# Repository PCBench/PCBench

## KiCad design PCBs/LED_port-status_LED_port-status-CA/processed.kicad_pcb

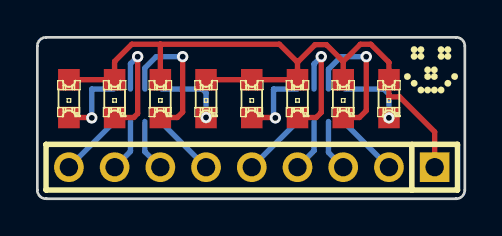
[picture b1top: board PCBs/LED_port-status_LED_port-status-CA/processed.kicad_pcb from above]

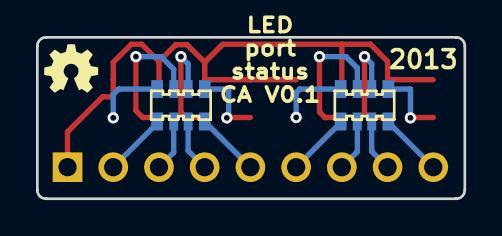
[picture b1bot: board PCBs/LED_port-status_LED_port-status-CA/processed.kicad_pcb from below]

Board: 2 copper layers, 23.7 x 9.0 mm, 13 parts (3 on the bottom side), 17 nets.

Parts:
D1, D2, D3, D4, D5, D6, D7, D8: LED; LED-0805
G1: LED_smile_silkscreen_3mm
G2: OSHW-logo_silkscreen_3mm
P1: CONN_9; SIL-9
RP1, RP2: 1k; MADW__1206*4_resistor_array

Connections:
unnamed: P1.9, RP1.4
unnamed: P1.8, RP1.3
unnamed: P1.7, RP1.2
unnamed: P1.6, RP1.1
unnamed: P1.5, RP2.4
unnamed: P1.4, RP2.3
unnamed: P1.3, RP2.2
unnamed: P1.2, RP2.1
unnamed: D1.2, RP1.5
unnamed: D6.2, RP2.6
unnamed: D8.2, RP2.8
unnamed: D5.2, RP2.5
unnamed: D4.2, RP1.8
unnamed: D2.2, RP1.6
unnamed: D7.2, RP2.7
unnamed: D3.2, RP1.7
unnamed: D1.1, D2.1, D3.1, D4.1, D5.1, D6.1, D7.1, D8.1, P1.1

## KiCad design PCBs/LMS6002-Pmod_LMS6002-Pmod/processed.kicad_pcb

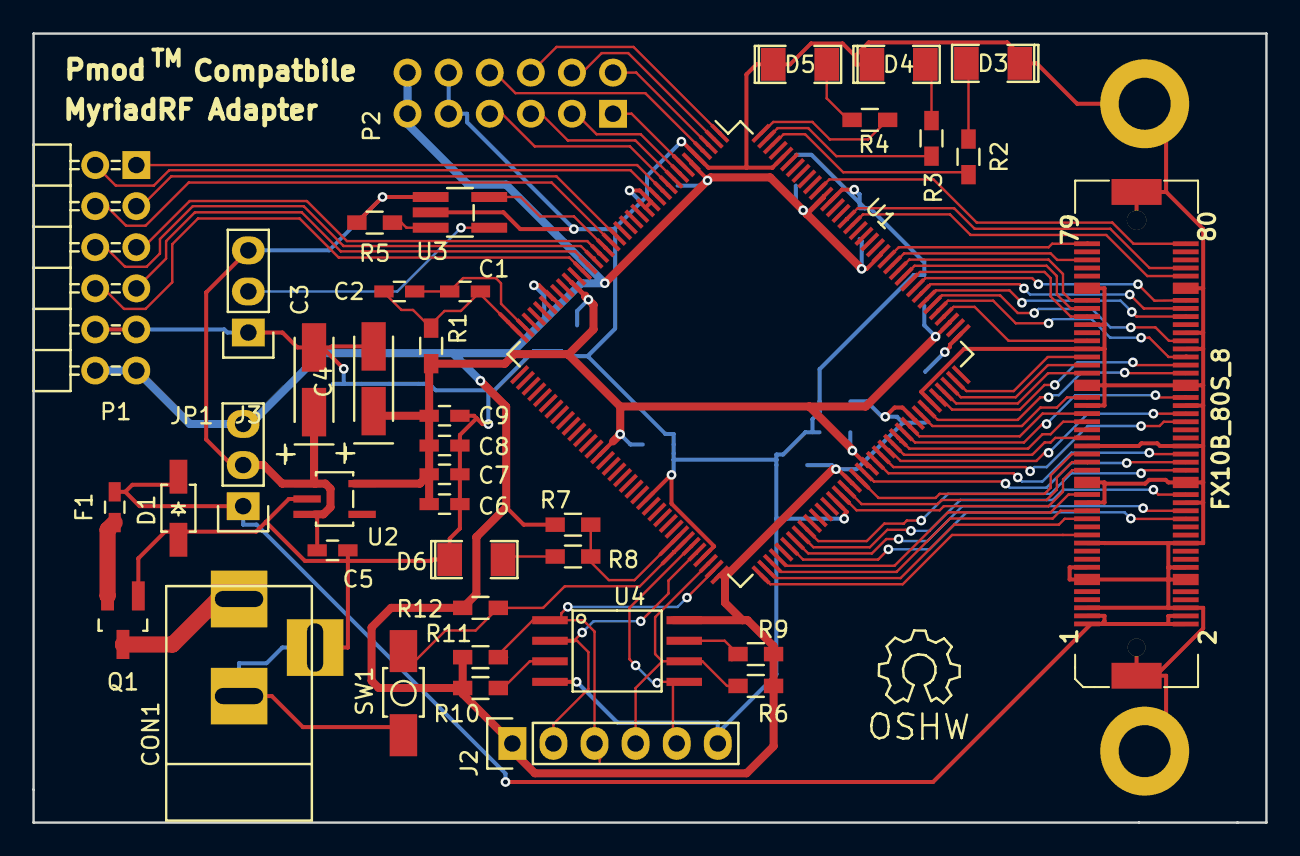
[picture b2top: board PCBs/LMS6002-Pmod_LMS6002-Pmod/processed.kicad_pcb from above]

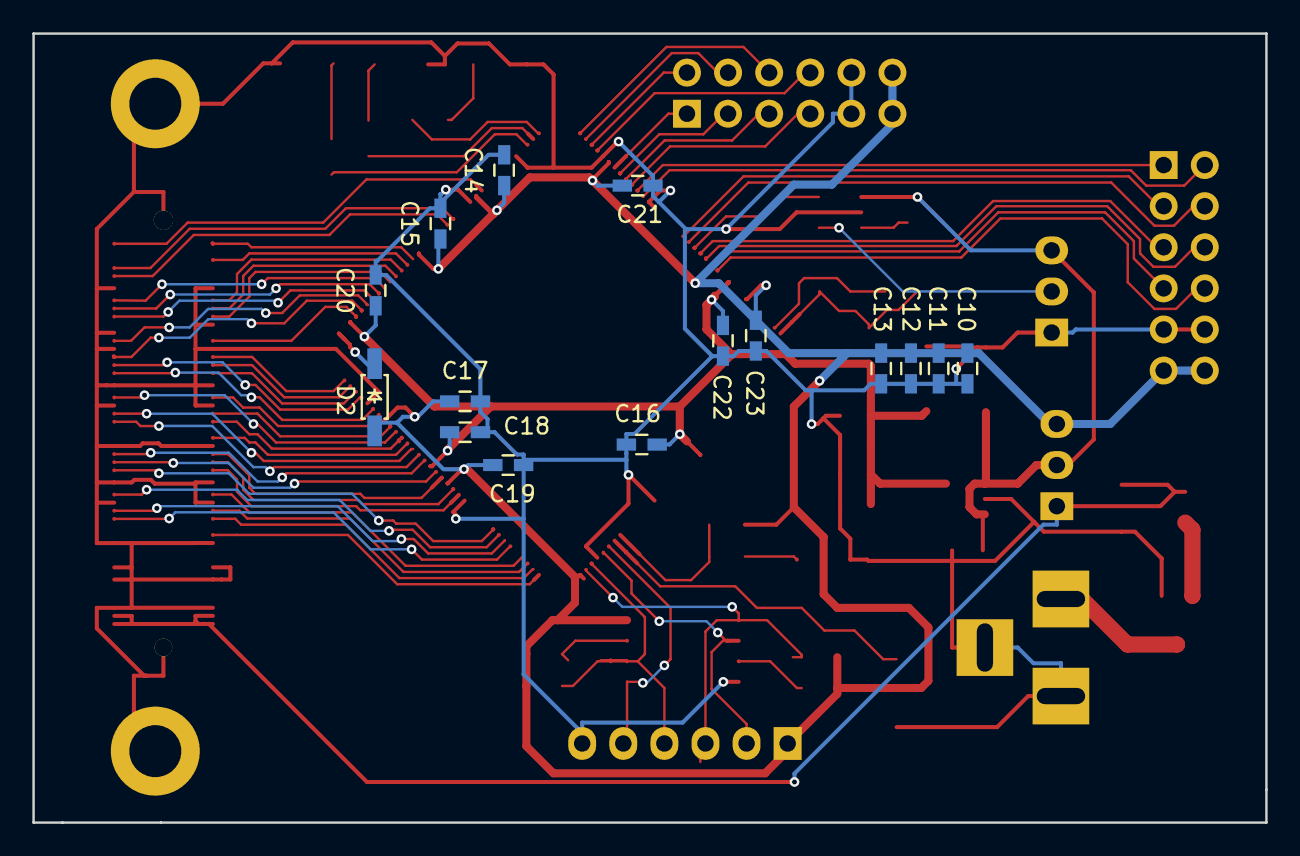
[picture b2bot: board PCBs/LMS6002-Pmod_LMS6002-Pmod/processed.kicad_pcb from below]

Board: 2 copper layers, 76.2 x 48.8 mm, 58 parts (15 on the bottom side), 83 nets.

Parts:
C1, C6, C10: 10µF; C_0603_HandSoldering
C2, C8, C12: 0.1µF; C_0603_HandSoldering
C3, C4: 1µF; TantalC_SizeA_EIA-3216_HandSoldering
C5: 0.1µ; C_0603_HandSoldering
C7, C11: 1µF; C_0603_HandSoldering
C9, C13: 0.01µF; C_0603_HandSoldering
C14, C15, C16, C17, C18, C19, C20, C21, C22, C23: 100n; C_0603_HandSoldering
CON1: BARREL_JACK
D1: 5V-SOD-123F; SOD-123F_Handsoldering
D2: Schottky 0520; SOD-123_Handsoldering
D3, D4, D5, D6: LED; SMD-1206_Pol
F1: 2A-0603; C_0603_HandSoldering
J1: FX10B_80S_8
J2: Pinheader_1x6_TH; Pin_Header_Straight_1x06
J3: SELECT_DIV; Pin_Header_Straight_1x03
JP1: LDO_1V2_IN_SEL; Pin_Header_Straight_1x03
P1: PMOD_2x6; Pmod
P2: PMOD_2x6; Pmod_no_header
P3, P4: Myriad_Mount_Hole
Q1: Q_PMOS_GSD; SOT-23_Handsoldering
R1: 100; R_0603_HandSoldering
R2, R3, R4, R8: 10; R_0603_HandSoldering
R5: R; R_0603_HandSoldering
R6, R9, R10, R11: 10k; R_0603_HandSoldering
R7, R12: 10K; R_0603_HandSoldering
SW1: ICE_RESET; B3U-1000P_Handsoldering
T1: OSHW_Logo; Symbol_OSHW-Logo_SilkScreen
U1: iCE40_1K4K_TQ144; TQFP-144_20x20mm_Pitch0.5mm
U2: LD6815; SOT-753_(TSOP-5)_Handsoldering
U3: LTC1799; TSOT-23_Handsoldering
U4: N25Q; SOP2-8_Handsoldering

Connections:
1V2_LDO: C4.1, C6.1, C7.1, C8.1, C9.1, C16.1, C18.1, C20.1, C22.1, R1.1, U1.27, U1.51, U1.92, U1.111, U2.5
3V3_PMOD: C10.1, C11.1, C12.1, C13.1, C14.1, C15.1, C17.1, C19.1, C21.1, C23.1, D2.2, J2.1, JP1.3, P1.6, P1.12, P2.6, P2.12, R6.1, R7.1, R9.1, R10.1, R11.1, R12.1, U1.6, U1.30, U1.72, U1.89, U1.100, U1.123, U1.133, U4.8
5V: D1.1, F1.2, J1.1, J1.2, J1.3, J1.4, JP1.1
5V_LDO_IN: C3.1, C5.1, J3.3, JP1.2, R5.2, U2.1, U2.3, U3.1
/power_supply/VIN: CON1.1, Q1.3
/power_supply/VIN_PROT: F1.1, Q1.2
DIQ1_D0: J1.23, U1.74
DIQ1_D1: J1.24, U1.78
DIQ1_D2: J1.25, U1.75
DIQ1_D3: J1.26, U1.79
DIQ1_D4: J1.29, U1.76
DIQ1_D5: J1.30, U1.80
DIQ1_D6: J1.31, U1.87
DIQ1_D7: J1.32, U1.81
DIQ1_D8: J1.33, U1.88
DIQ1_D9: J1.34, U1.91
DIQ1_D10: J1.35, U1.90
DIQ1_D11: J1.36, U1.93
DIQ1_SEL: J1.19, U1.73
DIQ2_D0: J1.43, U1.97
DIQ2_D1: J1.44, U1.94
DIQ2_D2: J1.45, U1.99
DIQ2_D3: J1.46, U1.95
DIQ2_D4: J1.49, U1.101
DIQ2_D5: J1.50, U1.98
DIQ2_D6: J1.51, U1.105
DIQ2_D7: J1.52, U1.102
DIQ2_D8: J1.53, U1.106
DIQ2_D9: J1.54, U1.104
DIQ2_D10: J1.55, U1.107
DIQ2_D11: J1.56, U1.113
DIQ2_SEL: J1.39, U1.96
EXT_SPI_CLK: J2.4, R6.2, U1.70, U4.6
EXT_SPI_MISO: J2.2, U1.68, U4.2
EXT_SPI_MOSI: J2.5, U1.67, U4.5
EXT_SPI_SS_B: J2.3, R11.2, U1.71, U4.1
FCLK1: J1.60, U1.114
FCLK2: J1.59, U1.112
GND: C3.2, C4.2, C5.2, C6.2, C7.2, C8.2, C9.2, C10.2, C11.2, C12.2, C13.2, C14.2, C15.2, C16.2, C17.2, C18.2, C19.2, C20.2, C21.2, C22.2, C23.2, CON1.2, CON1.3, D1.2, D3.1, D4.1, D5.1, D6.1, J1.5, J1.6, J1.11, J1.12, J1.17, J1.18, J1.27, J1.28, J1.37, J1.38, J1.47, J1.48, J1.57, J1.58, J1.62, J1.63, J1.81, J1.82, J1.83, J1.84, J1.85, J1.86, J1.87, J1.88, J1.89, J1.90, J2.6, J3.1, P1.5, P1.11, P2.5, P2.11, P3.GND, P4.GND, Q1.1, SW1.1, U1.5, U1.13, U1.14, U1.59, U1.69, U1.86, U1.103, U1.132, U1.140, U2.2, U3.2, U4.4
ICE_CDONE: R7.2, R8.1, U1.65
ICE_CLK_IN: U1.21, U3.5
ICE_CRESET_B: R12.2, SW1.2, U1.66
unnamed: C1.1, C2.1, U1.35
unnamed: C1.2, C2.2, R1.2, U1.36
unnamed: D2.1, U1.109
unnamed: D3.2, R2.1
unnamed: D4.2, R3.1
unnamed: D5.2, R4.1
unnamed: D6.2, R8.2
unnamed: J3.2, U3.4
unnamed: R2.2, U1.142
unnamed: R3.2, U1.143
unnamed: R4.2, U1.144
unnamed: R5.1, U3.3
unnamed: R9.2, U4.7
unnamed: R10.2, U4.3
PIO0: P1.1, U1.11
PIO1: P1.2, U1.19
PIO2: P1.3, U1.22
PIO3: P1.4, U1.24
PIO4: P1.7, U1.12
PIO5: P1.8, U1.20
PIO6: P1.9, U1.23
PIO7: P1.10, U1.25
PIO8: P2.1, U1.7
PIO9: P2.2, U1.8
PIO10: P2.3, U1.9
PIO11: P2.4, U1.10
PIO12: P2.7, U1.3
PIO13: P2.8, U1.2
PIO14: P2.9, U1.1
PIO15: P2.10, U1.4
RFDIO_GPIO0: J1.65, U1.118
RFDIO_GPIO1: J1.67, U1.119
RFDIO_GPIO2: J1.69, U1.120
RFDIO_REF_CLK_IN: J1.75, U1.121
RFDIO_RESET: J1.66, U1.115
RFDIO_SPI_CLK: J1.72, U1.128
RFDIO_SPI_EN: J1.74, U1.129
RFDIO_SPI_MISO: J1.70, U1.117
RFDIO_SPI_MOSI: J1.68, U1.116
RXEN: J1.80, U1.134
TXEN: J1.79, U1.122

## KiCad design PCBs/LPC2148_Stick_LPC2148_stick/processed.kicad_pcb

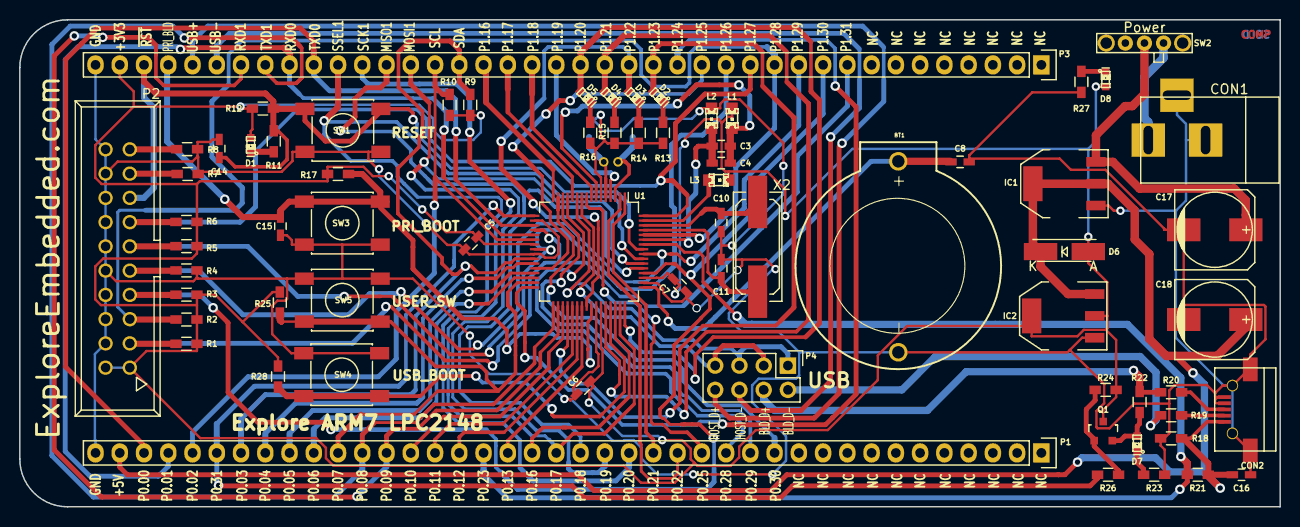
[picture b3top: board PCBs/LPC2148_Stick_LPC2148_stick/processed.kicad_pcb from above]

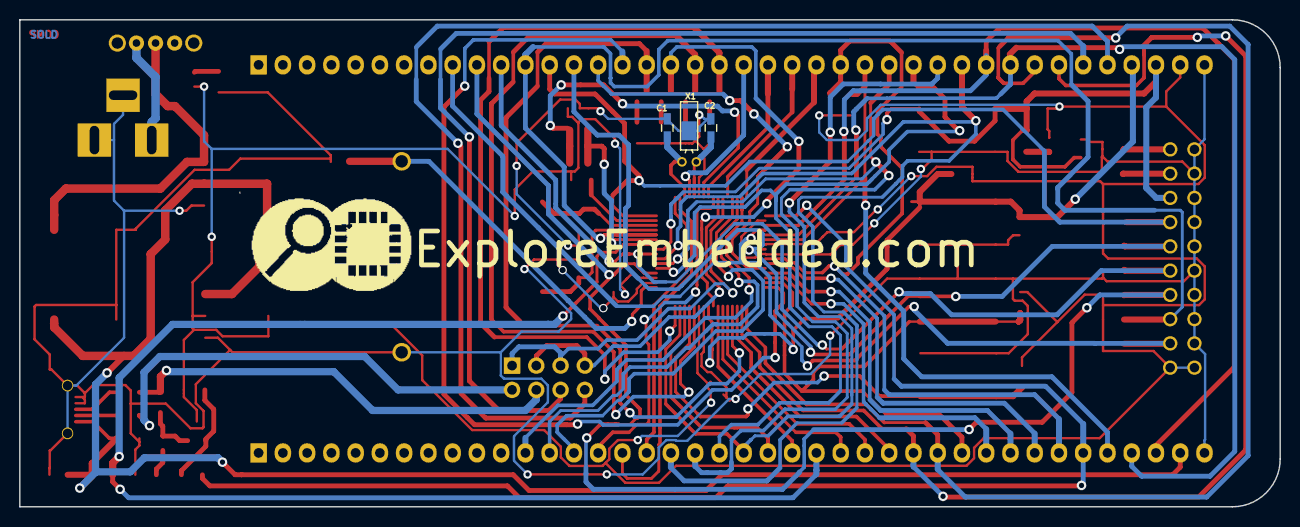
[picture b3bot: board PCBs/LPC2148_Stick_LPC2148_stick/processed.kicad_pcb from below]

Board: 2 copper layers, 132.0 x 51.0 mm, 73 parts (4 on the bottom side), 78 nets.

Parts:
BT1: CR2032; BATT_rtc_XL
C1, C2, C10, C11: 22pf; C_0603_HandSoldering
C3: 4.7uF; C_0603_HandSoldering
C4, C5, C6, C7, C8, C14, C15, C16: 100nf; C_0603_HandSoldering
C17, C18: 100uF/25V; c_elec_8x10.5
CON1: BARREL_JACK
CON2: USB-MINI-B; USB_Micro-B_SMD
D1, D7: LED_Rst; LED-0603_NEW
D2, D3, D4, D5: LED; LED-0603_NEW
D6: 1n4148; ZenerDiode_SMD
D8: PWR; LED-0603_NEW
EE_LOGO: EE_LOGO(2)
IC1, IC2: LM1117; SOT-223
L1, L2, L3: FER; LED-0805
P1, P3: CONN_01X40; Pin_Header_Straight_1x40
P2: JTAG; VASCH10x2
P4: USB Operation Selection; Pin_Header_Straight_2x04
Q1: BC856; SOT-23
R1, R2, R3, R4, R5, R6, R7, R8, R12, R21, R24, R25, R28: 10K; R_0603_HandSoldering
R9, R10, R26: 2K; R_0603_HandSoldering
R11, R17: 1K; R_0603_HandSoldering
R13, R14, R15, R16, R23, R27: 470E; R_0603_HandSoldering
R18: 100K; R_0603_HandSoldering
R19, R20: 33E; R_0603_HandSoldering
R22: 1K5; R_0603_HandSoldering
SW1: RST; SW_PUSH_SMALL_smd_NEW
SW2: Power; Micro_slide_switch-spst_2mm_new
SW3, SW4: ISP; SW_PUSH_SMALL_smd_NEW
SW5: User Sw1; SW_PUSH_SMALL_smd_NEW
U1: LPC2148; LQFP-64_10x10mm_Pitch0.5mm
X1: 3.768KHz; Crystal_Round_Horizontal_2mm_NEW
X2: 12MHz; Q_49U3HMS

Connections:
+3.3VP: C5.2, C6.2, C7.2, D1.1, D6.1, D8.1, IC2.2, IC2.4, L1.2, L3.1, P2.1, P2.2, P3.39, Q1.3, R1.2, R2.2, R3.2, R5.2, R6.2, R9.2, R10.2, R12.2, R17.2, R24.2, R25.2, R28.2, U1.23, U1.43, U1.51
+5V: C16.1, C18.1, CON2.1, D6.2, IC1.2, IC1.4, IC2.3, P1.39, R18.1, R21.2
/CONNECT: P1.35, R26.2, U1.17
/MISO1: P1.20, P3.28, U1.53
/MOSI1: P1.19, P3.27, U1.54
/RTCK: P2.11, P3.14, R5.1, U1.24
/RXD0: P1.37, P3.32, U1.21
/RXD1: P1.28, P3.34, U1.34
/SCK1: P1.21, P3.29, U1.47
/SCL0: P1.36, P3.26, R10.1, U1.22
/SDA0: P1.34, P3.25, R9.1, U1.26
/SSEL1: P1.18, P3.30, U1.55
/TCK: P2.9, P3.11, R4.1, U1.56
/TD0: P2.13, P3.13, R6.1, U1.64
/TDI: P2.5, P3.12, R2.1, U1.60
/TMS: P2.7, P3.10, R3.1, U1.52
/TXD0: P1.38, P3.31, U1.19
/TXD1: P1.29, P3.33, U1.33
/VBUS: P1.24, R21.1, U1.58
/VDDA: C3.2, C4.2, L1.1, U1.7
/u_led_1: D2.1, P3.17, U1.36
/u_led_2: D3.1, P3.18, U1.40
/u_led_3: D4.1, P3.19, U1.44
/u_led_4: D5.1, P3.20, U1.48
/u_sw_1: P1.30, R25.1, SW5.2, U1.31
/~RST: C14.2, P2.15, P3.38, R11.2, R12.1, SW1.2, U1.57
/~TRST: P2.3, P3.9, R1.1, U1.20
GND: BT1.2, C1.2, C2.2, C5.1, C6.1, C7.1, C8.2, C10.2, C11.1, C14.1, C15.1, C16.2, C17.2, C18.2, CON1.2, CON1.3, CON2.4, CON2.5, CON2.6, CON2.7, CON2.8, CON2.9, IC1.1, IC2.1, L2.2, P1.40, P2.4, P2.6, P2.8, P2.10, P2.12, P2.14, P2.16, P2.18, P2.20, P3.40, R4.2, R7.2, R8.2, R13.2, R14.2, R15.2, R16.2, R18.2, R23.1, R27.1, SW1.1, SW3.1, SW4.1, SW5.1, U1.6, U1.18, U1.25, U1.42, U1.50, X1.3
HOST_USB_D+: P3.36, P4.8
HOST_USB_D-: P3.35, P4.6
unnamed: BT1.1, C8.1, U1.49
unnamed: C1.1, U1.3, X1.1
unnamed: C2.1, U1.5, X1.2
unnamed: C3.1, C4.1, L2.1, U1.59
unnamed: C10.1, U1.62, X2.1
unnamed: C11.2, U1.61, X2.2
unnamed: C17.1, IC1.3, SW2.2
unnamed: CON1.1, SW2.1
unnamed: CON2.2, R19.2
unnamed: CON2.3, R20.2
unnamed: D1.2, R11.1
unnamed: D2.2, R13.1
unnamed: D3.2, R14.1
unnamed: D4.2, R15.1
unnamed: D5.2, R16.1
unnamed: D7.1, Q1.2, R22.2
unnamed: D7.2, R23.2
unnamed: D8.2, R27.2
unnamed: L3.2, U1.63
unnamed: P1.12, U1.15
unnamed: P1.13, U1.14
unnamed: P1.14, U1.13
unnamed: P1.15, U1.9
unnamed: P1.16, U1.2
unnamed: P1.17, U1.1
unnamed: P1.22, U1.46
unnamed: P1.23, U1.39
unnamed: P1.25, U1.38
unnamed: P1.26, U1.37
unnamed: P1.27, U1.35
unnamed: P1.31, U1.30
unnamed: P1.32, U1.29
unnamed: P1.33, U1.27
unnamed: P2.17, R7.1
unnamed: P2.19, R8.1
unnamed: P3.15, U1.28
unnamed: P3.16, U1.32
unnamed: P3.21, U1.4
unnamed: P3.22, U1.8
unnamed: P3.23, U1.12
unnamed: P3.24, U1.16
unnamed: P4.2, R19.1
unnamed: P4.4, R20.1, R22.1
unnamed: Q1.1, R24.1, R26.1
PRI_BLD: C15.2, P3.37, R17.1, SW3.2, U1.41
USB_BLD: R28.1, SW4.2, U1.45
USB_D+: P4.3, P4.7, U1.10
USB_D-: P4.1, P4.5, U1.11

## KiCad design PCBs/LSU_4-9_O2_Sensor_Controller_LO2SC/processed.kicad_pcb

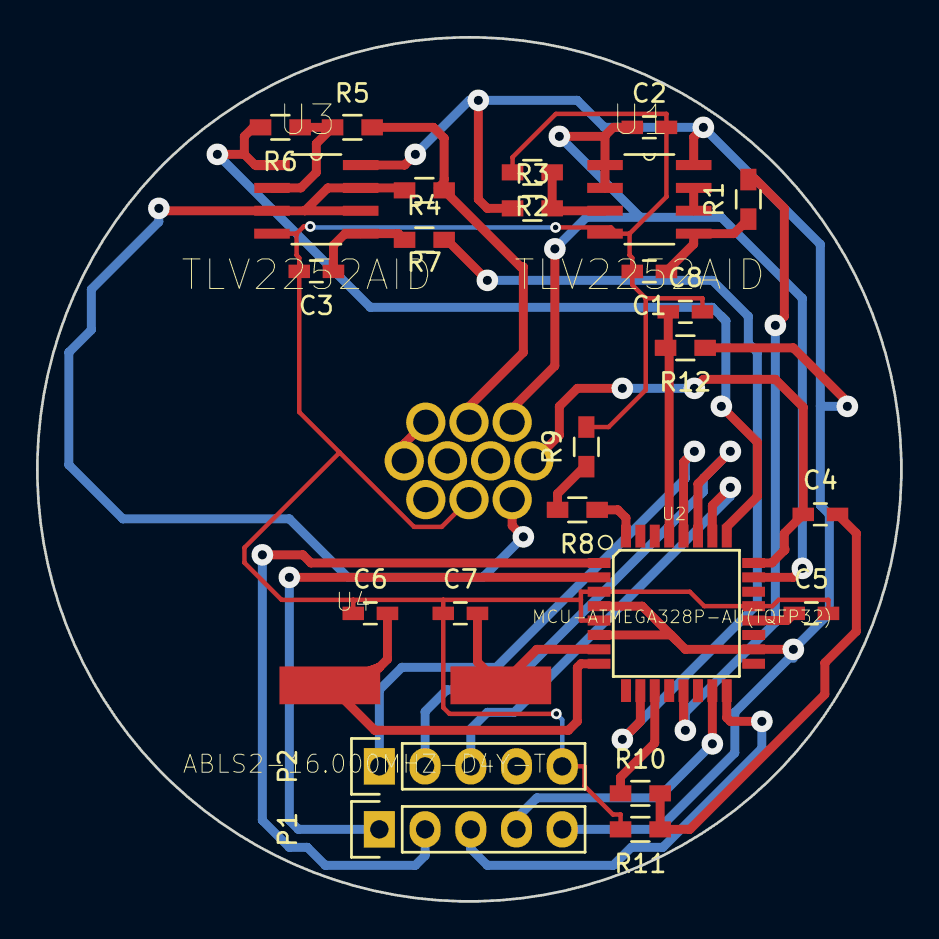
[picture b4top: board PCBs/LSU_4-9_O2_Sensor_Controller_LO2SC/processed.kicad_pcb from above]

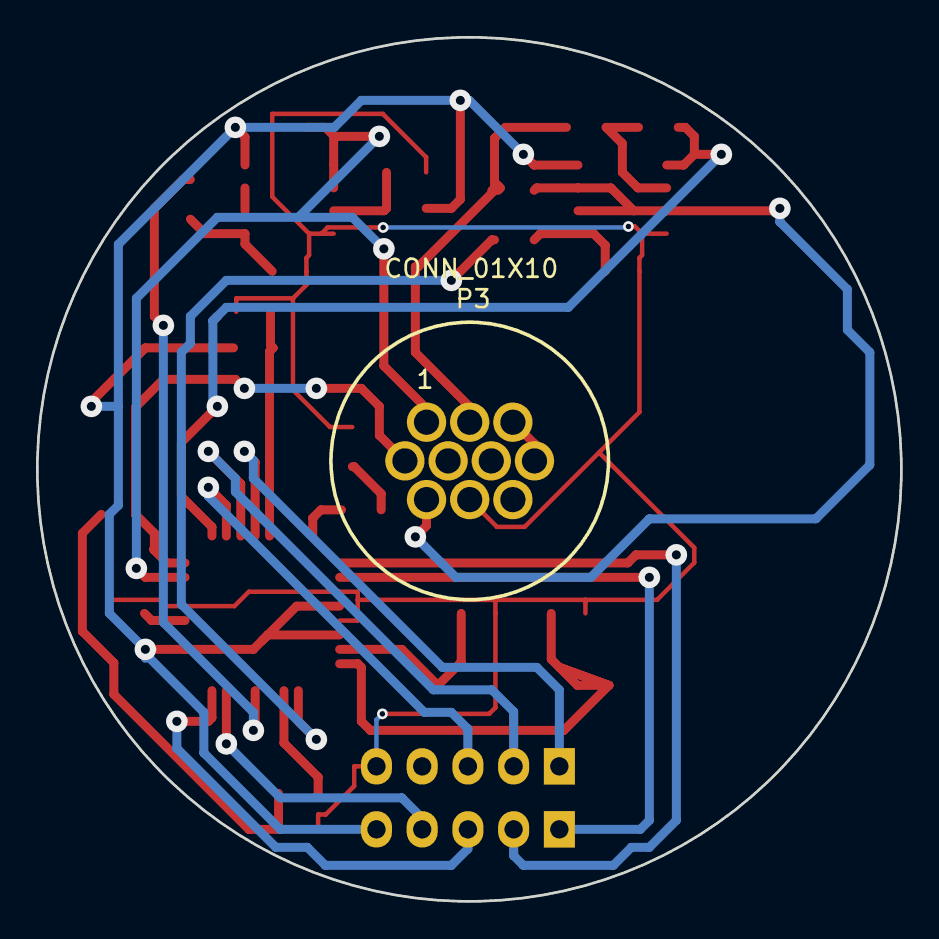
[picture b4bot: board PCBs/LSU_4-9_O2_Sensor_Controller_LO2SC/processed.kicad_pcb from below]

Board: 2 copper layers, 48.0 x 48.0 mm, 28 parts (2 on the bottom side), 30 nets.

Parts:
C1, C3: 10nF; C_0603_HandSoldering
C2, C4, C5, C8: 100nF; C_0603_HandSoldering
C6, C7: 1nF; C_0603_HandSoldering
P1, P2: CONN_01X05; Pin_Header_Straight_1x05
P3: CONN_01X10; JAE_10Pins
R1, R4: 470k; R_0603_HandSoldering
R2, R3: 1.2k; R_0603_HandSoldering
R5: 22k; R_0603_HandSoldering
R6: 330k; R_0603_HandSoldering
R7: 62; R_0603_HandSoldering
R8: 47k; R_0603_HandSoldering
R9, R10, R11, R12: 10k; R_0603_HandSoldering
Ref**: Val**; vue3D
U1, U3: TLV2252AID; SOIC127P600X175-8N
U2: MCU-ATMEGA328P-AU(TQFP32); TQFP32-0.8-7X7MM
U4: ABLS2-16.000MHZ-D4Y-T; HC-49

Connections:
2.5v: C2.1, P3.1, U1.1, U1.2, U2.23
+5V: P1.5, R3.1, R12.1, U1.8, U2.4, U2.6, U2.18, U3.8
CSEL0: P2.2, U2.27
CSEL1: P2.3, U2.26
CSEL2: P1.3, U2.16
DSEL: P1.4, U2.15
GND: C1.2, C2.2, C3.2, C5.2, C6.1, C7.1, C8.2, P2.5, P3.9, R2.2, R9.2, R11.2, U1.4, U2.3, U2.5, U2.21, U3.4
H+: P3.3, P3.7
IP: P3.2, R5.2, R7.1
LATCH: P2.1, U2.28
unnamed: C1.1, R1.1, U1.5
unnamed: C3.1, R4.1, U3.5
unnamed: C4.2, R10.2, R11.1
unnamed: C5.1, U2.20
unnamed: C6.2, U2.8, U4.1
unnamed: C7.2, U2.7, U4.2
unnamed: C8.1, R12.2, U2.29
unnamed: R2.1, R3.2, U1.3
unnamed: R5.1, R6.1, U3.2
OUT_LINEAR: U1.6, U1.7
OUT_NARROWBAND: R8.2, R9.1
PIN_IPA: R6.2, U2.25, U3.1
PIN_VS: C4.1, P3.4, U2.24
POUT_IP: R4.2, U2.10
POUT_NARROW: R8.1, U2.32
POUT_VS: R10.1, U2.11
POUT_WIDE: R1.2, U2.13
RCAL: P3.8, R7.2, U3.3, U3.6, U3.7
SCLK: P1.2, U2.1
SIN: P1.1, U2.2

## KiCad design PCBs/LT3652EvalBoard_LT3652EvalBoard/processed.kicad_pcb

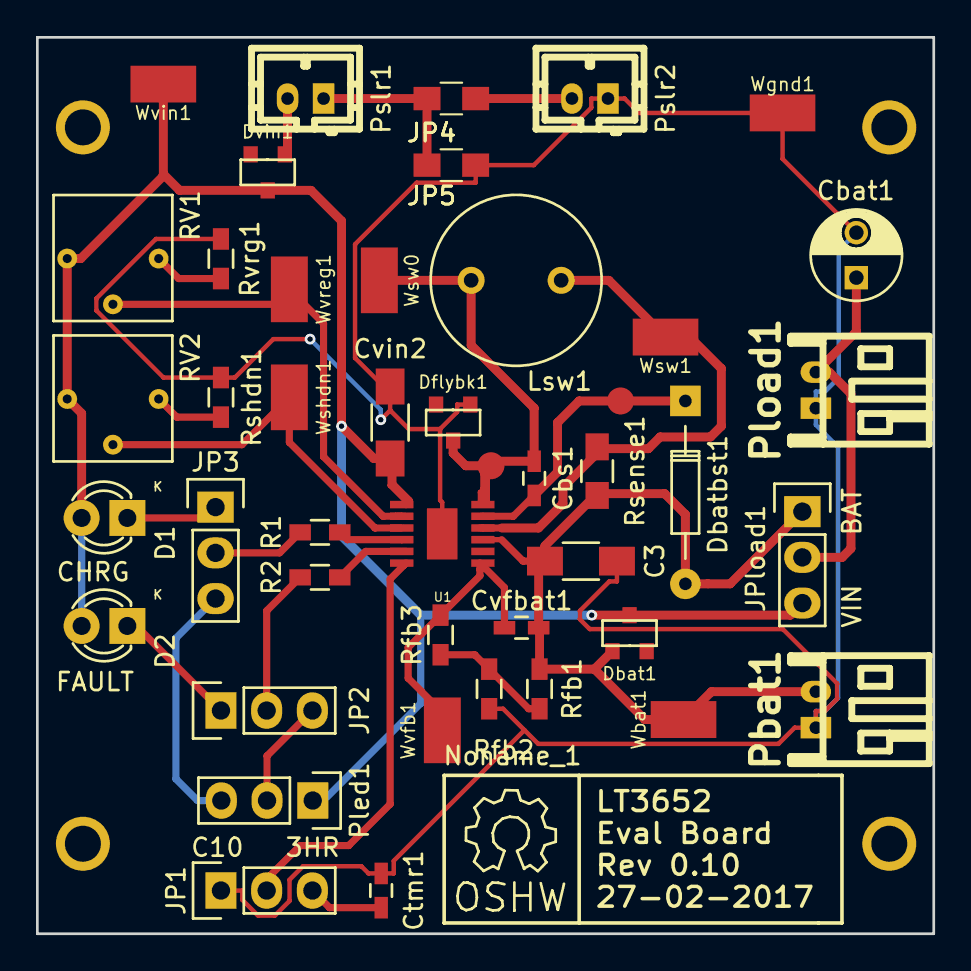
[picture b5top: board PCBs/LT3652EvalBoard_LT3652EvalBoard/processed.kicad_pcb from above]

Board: 2 copper layers, 49.8 x 49.8 mm, 46 parts (0 on the bottom side), 26 nets.

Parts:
C3: 10uF; C_1206_HandSoldering
Cbat1: 100uF; C_Radial_D5_L6_P2.5
Cbs1: 1uF; C_0603_HandSoldering
Ctmr1: 0.68µF; C_0603_HandSoldering
Cvfbat1: 22pF; C_0603_HandSoldering
Cvin2: 10uF; C_1206_HandSoldering
D1: 3mm GRN; LED-3MM
D2: 3mm RED; LED-3MM
Dbat1: D_Schottky_Small_ZLLS500; DIODES_INC_ZLLS500
Dbatbst1: D_Small; Diode_DO-35_SOD27_Horizontal_RM10
Dflybk1: ZLLS500; DIODES_INC_ZLLS500
Dvin1: ZLLS500; DIODES_INC_ZLLS500
JP1: TIMER OPT; Pin_Header_Straight_1x03
JP2, JP3: JUMPER3; Pin_Header_Straight_1x03
JP4: Jumper_NO_Small; R_0805_HandSoldering
JP5: Jumper_NC_Small; R_0805_HandSoldering
JPload1: JUMPER3; Pin_Header_Straight_1x03
Lsw1: 10uH; PANASONIC_ELC09D100F
Noname_1: Symbol_OSHW-Logo_SilkScreen
Pbat1: JST PH; s2b-ph-kl
Pled1: CONN_01X03; Pin_Header_Straight_1x03
Pload1: JST PH; s2b-ph-kl
Pslr1, Pslr2: JST PH; b2b-ph-kl
R1, R2: 10K; R_0603_HandSoldering
RV1, RV2: POT; Bourns_3362P_Trimmer
Rfb1: 90k; R_0603_HandSoldering
Rfb2: 330k; R_0603_HandSoldering
Rfb3: 179k; R_0603_HandSoldering
Rsense1: 250mO; R_0805_HandSoldering
Rshdn1: 10K; R_0603_HandSoldering
Rvrg1: 10K; R_0603_HandSoldering
U1: LT3652; LT3652MSE_HandSoldering
Wbat1: TEST_1P; HARWIN_S1751-46
Wbst1: TEST_1P; Measurement_Point_Round-SMD-Pad_Small
Wgnd1: TEST_1P; HARWIN_S1751-46
Wshdn1: TEST_1P; HARWIN_S1751-46
Wsw0, Wsw1: TEST_1P; HARWIN_S1751-46
Wsw2: TEST_1P; Measurement_Point_Round-SMD-Pad_Small
Wvfb1: TEST_1P; HARWIN_S1751-46
Wvin1: TEST_1P; HARWIN_S1751-46
Wvreg1: TEST_1P; HARWIN_S1751-46

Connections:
/BAT: C3.1, Cvfbat1.1, Dbat1.3, Dbatbst1.2, JPload1.1, Pbat1.2, Rfb1.1, Rsense1.2, U1.9, Wbat1.1
/BOOST: Cbs1.1, Dbatbst1.1, U1.11, Wbst1.1
/SENSE: Lsw1.2, Rsense1.1, U1.10, Wsw1.1
/SHDN: RV2.2, U1.3, Wshdn1.1
/SW: Cbs1.2, Dflybk1.1, Lsw1.1, U1.12, Wsw0.1, Wsw2.1
/VFB: Cvfbat1.2, Rfb3.2, U1.7, Wvfb1.1
/VIN: Cvin2.2, D1.2, D2.2, Dbat1.1, Dvin1.1, JPload1.3, Pled1.1, RV1.1, RV2.1, U1.1, Wvin1.1
/VIN_REG: RV1.2, U1.2, Wvreg1.1
GND: C3.2, Cbat1.2, Ctmr1.2, Cvin2.1, Dflybk1.3, JP1.1, JP5.1, Pbat1.1, Pload1.1, Pslr2.1, Rfb2.2, Rshdn1.2, Rvrg1.2, U1.13, Wgnd1.1
unnamed: Cbat1.1, JPload1.2, Pload1.2
unnamed: Ctmr1.1, JP1.3
unnamed: D1.1, JP3.1
unnamed: D2.1, JP2.1
unnamed: Dvin1.3, Pslr1.2
unnamed: JP1.2, U1.6
unnamed: JP2.2, R2.2
unnamed: JP2.3, Pled1.2
unnamed: JP3.2, R1.2
unnamed: JP3.3, Pled1.3
unnamed: JP4.1, JP5.2, Pslr1.1
unnamed: JP4.2, Pslr2.2
unnamed: R1.1, U1.4
unnamed: R2.1, U1.5
unnamed: RV1.3, Rvrg1.1
unnamed: RV2.3, Rshdn1.1
unnamed: Rfb1.2, Rfb2.1, Rfb3.1
